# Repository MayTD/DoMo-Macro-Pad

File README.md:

# DoMo Macro Pad

DoMo is a 3x3 macro pad with a rotary encoder and OLED display. It's a straightforward design with a straightforward idea. I originally designed this for myself to provide quick access to most commonly used keys especially for programming. That means the top priority were to include shortcuts for copy and paste! However this can also be used just as any other macro pads for media controls to help improve workflow.

QMK: https://github.com/MayTD/qmk_firmware/tree/master/keyboards/domo

## Features

- QMK Firmware Support
- MX Hot Swap
- OLED Screen
- Rotary Encoder
- LEDS

## Assembly 
Note that source files only covers the PCB. Components must be assembled in order for the board to be functional or completed.
| Number of Parts | Component | Description |
| ------------- | ------------- | ------------- |
| 1 | USB Cable  | Depends on choice of microcontrollers |
| 1 | Pro Micro or Equivalent | Microcontroller that features USB connectivity on-board |
| 1 | Reset Switch | Switch to enter bootloader mode |
| 10 | Diodes | standard switching signal diode | 
| 9 | Kailh MX Sockets | Hot Swapping Sockets which can support MX switches |
| 9 | MX switches | PCB supports PCB Mounted switches | 
| 1 | Rotary Encoder | EC11, 5Pin, 6mm |
| 9 | Keycaps | Any keycaps of choice |
| 1 | Bottom Plate | PCB includes 4 mounting holes that could fit M2 screws | 
| 4 | LEDS | Individual WS2812B 5050 RGB LEDs|
| 4 | 1x4 Connector | 4 pin male header|
| 1 | OLED Display | 0.91 128×32 Display Module|

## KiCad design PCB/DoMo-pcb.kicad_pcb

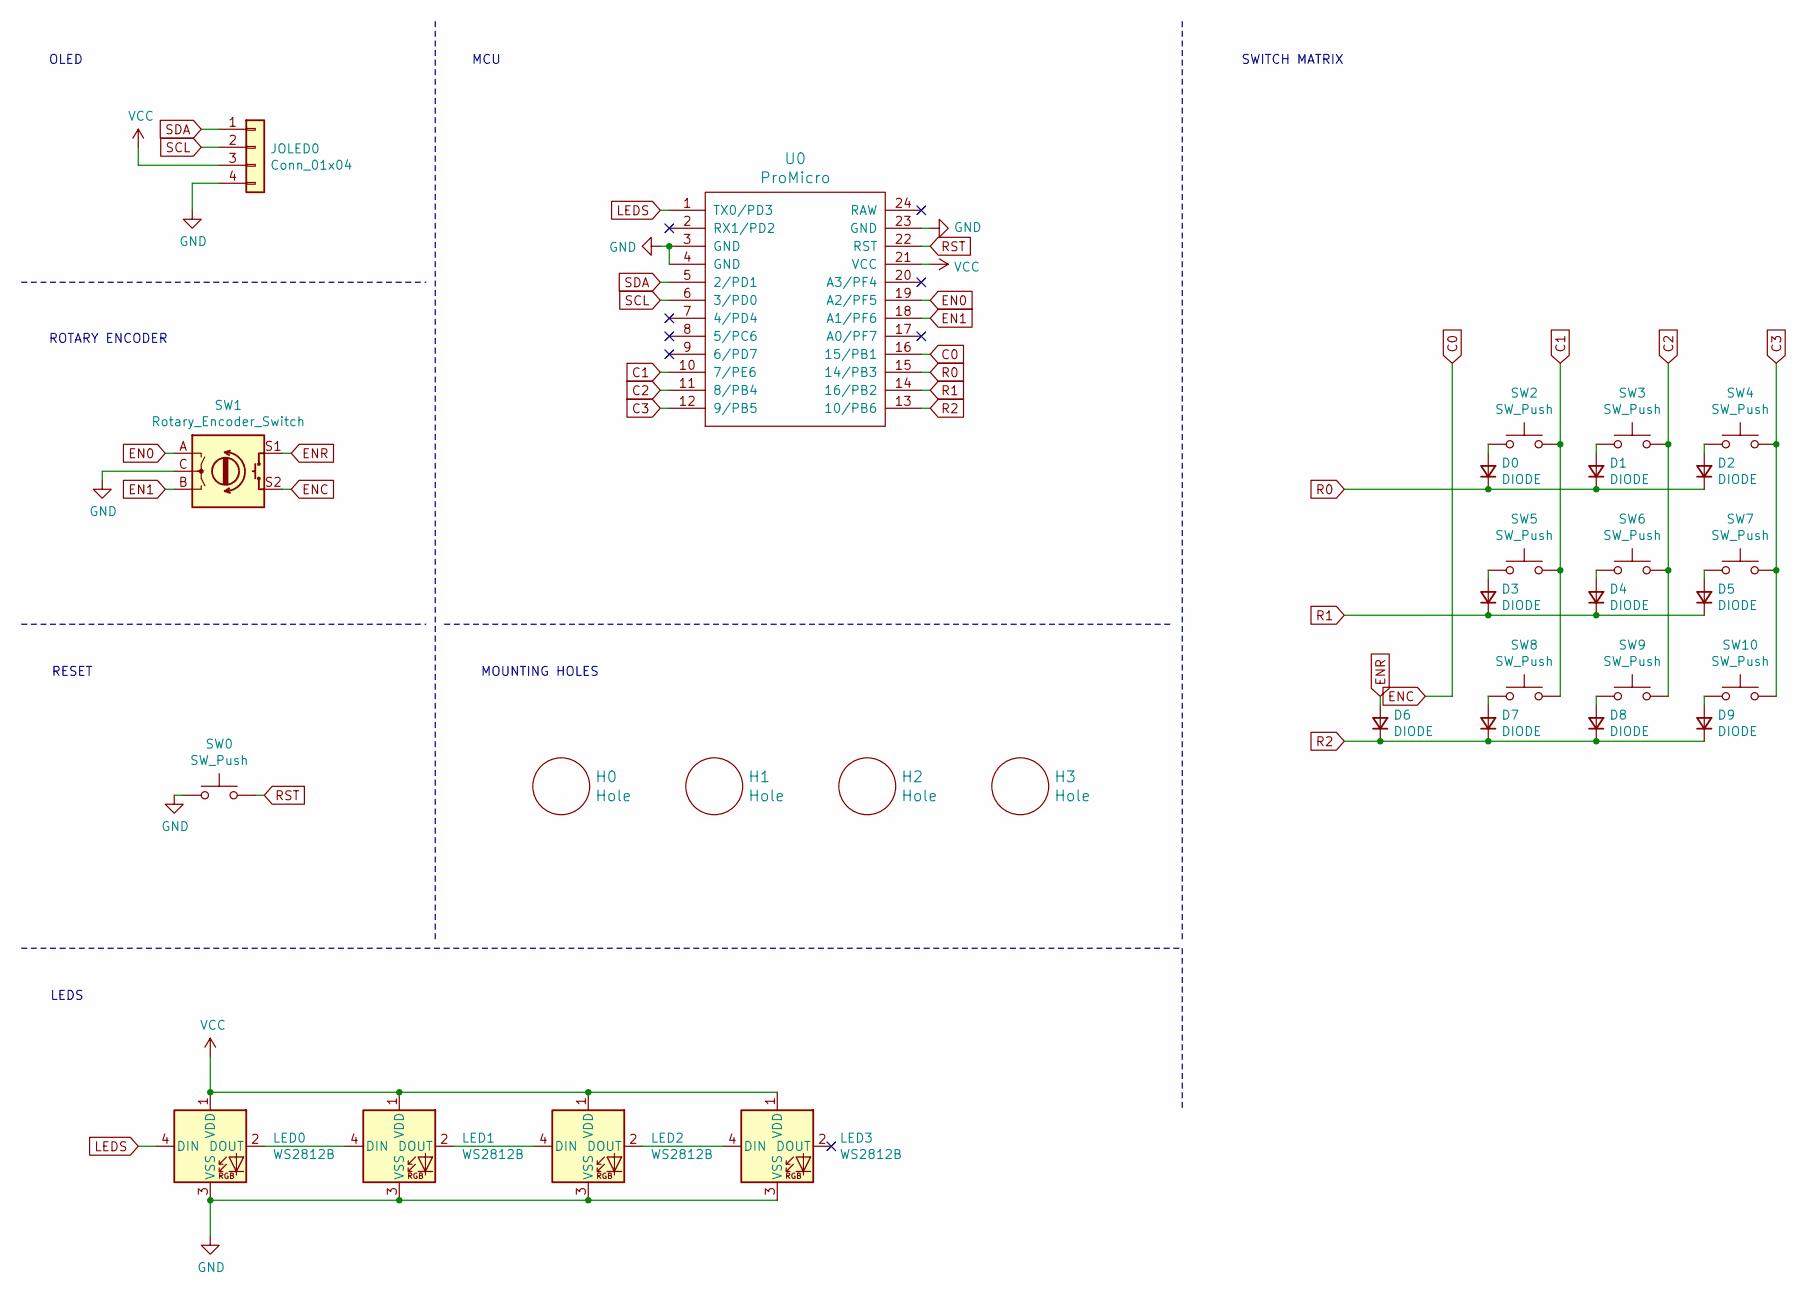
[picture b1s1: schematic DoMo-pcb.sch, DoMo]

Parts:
D0, D1, D2, D3, D4, D5, D6, D7, D8, D9: DIODE; MD_Diode
H0, H1, H2, H3: Hole; MountingHole_2.2mm_M2
JOLED0: Conn_01x04; Pin_Header_Straight_1x04_Pitch2.54mm
LED0, LED1, LED2, LED3: WS2812B; LED_WS2812B-PLCC4
SW0: SW_Push; SW_PUSH_6mm
SW1: Rotary_Encoder_Switch; RotaryEncoder_Alps_EC11E-Switch_Vertical_H20mm
SW2, SW3, SW4, SW5, SW6, SW7, SW8, SW9, SW10: SW_Push; MXOnly-1U-Hotswap
U0: ProMicro; ArduinoProMicro

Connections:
C0: SW1.S2, U0.16 (15/PB1)
C1: SW2.2, SW5.2, SW8.2, U0.10 (7/PE6)
C2: SW3.2, SW6.2, SW9.2, U0.11 (8/PB4)
C3: SW4.2, SW7.2, SW10.2, U0.12 (9/PB5)
EN0: SW1.A, U0.19 (A2/PF5)
EN1: SW1.B, U0.18 (A1/PF6)
ENR: D6.2 (A), SW1.S1
GND: JOLED0.4, LED0.3 (VSS), LED1.3 (VSS), LED2.3 (VSS), LED3.3 (VSS), SW0.1, SW1.C, U0.3 (GND), U0.4 (GND), U0.23 (GND)
LEDS: LED0.4 (DIN), U0.1 (TX0/PD3)
unnamed: D0.2 (A), SW2.1
unnamed: D1.2 (A), SW3.1
unnamed: D2.2 (A), SW4.1
unnamed: D3.2 (A), SW5.1
unnamed: D4.2 (A), SW6.1
unnamed: D5.2 (A), SW7.1
unnamed: D7.2 (A), SW8.1
unnamed: D8.2 (A), SW9.1
unnamed: D9.2 (A), SW10.1
unnamed: LED0.2 (DOUT), LED1.4 (DIN)
unnamed: LED1.2 (DOUT), LED2.4 (DIN)
unnamed: LED2.2 (DOUT), LED3.4 (DIN)
R0: D0.1 (K), D1.1 (K), D2.1 (K), U0.15 (14/PB3)
R1: D3.1 (K), D4.1 (K), D5.1 (K), U0.14 (16/PB2)
R2: D6.1 (K), D7.1 (K), D8.1 (K), D9.1 (K), U0.13 (10/PB6)
RST: SW0.2, U0.22 (RST)
SCL: JOLED0.2, U0.6 (3/PD0)
SDA: JOLED0.1, U0.5 (2/PD1)
VCC: JOLED0.3, LED0.1 (VDD), LED1.1 (VDD), LED2.1 (VDD), LED3.1 (VDD), U0.21 (VCC)

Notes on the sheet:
OLED
LEDS
ROTARY ENCODER
RESET
SWITCH MATRIX
MCU
MOUNTING HOLES

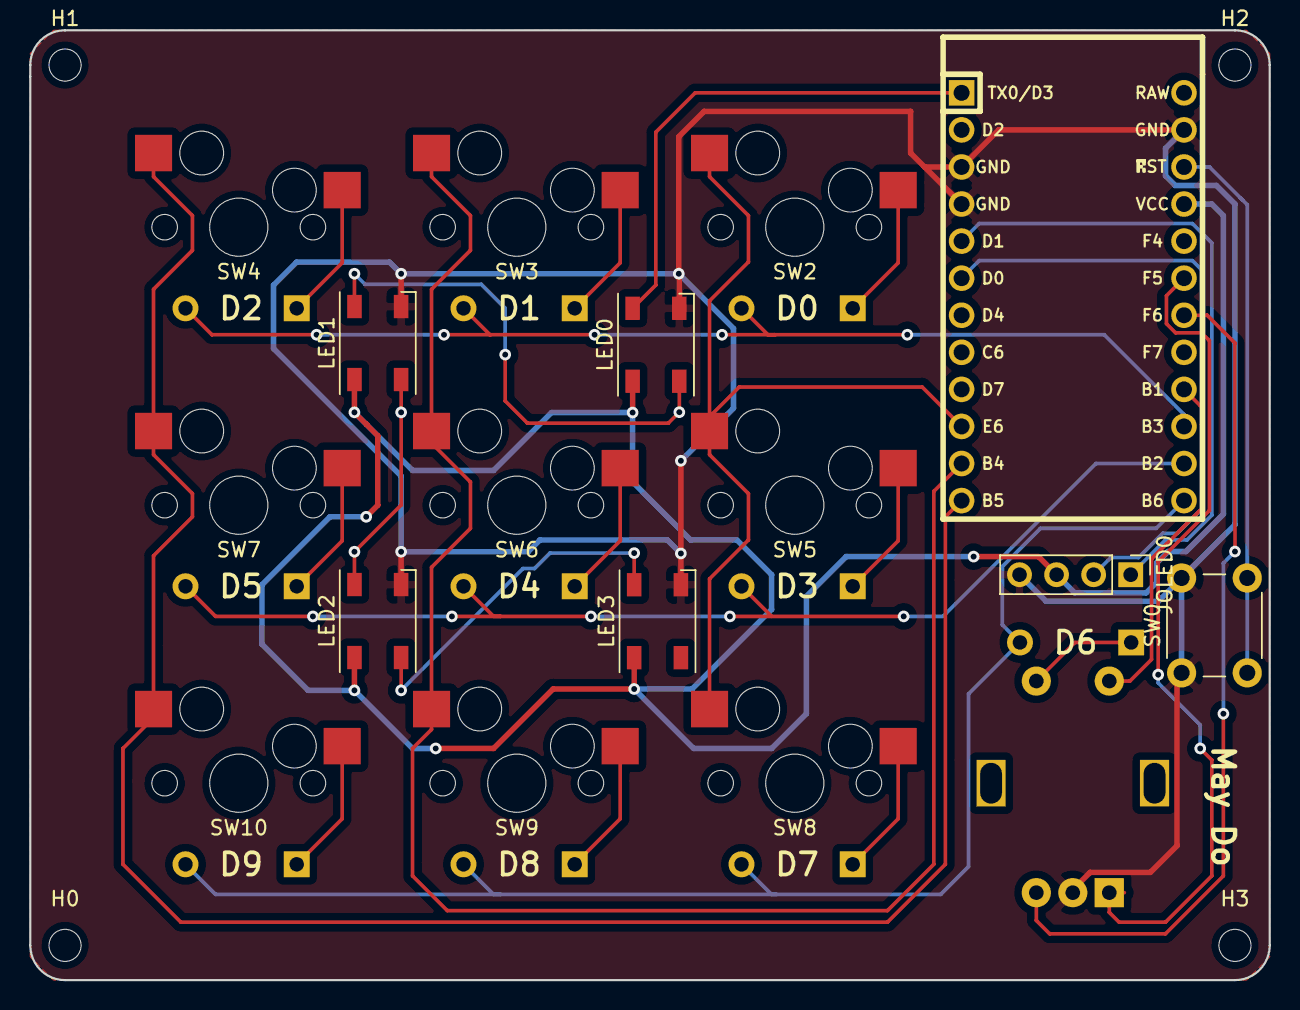
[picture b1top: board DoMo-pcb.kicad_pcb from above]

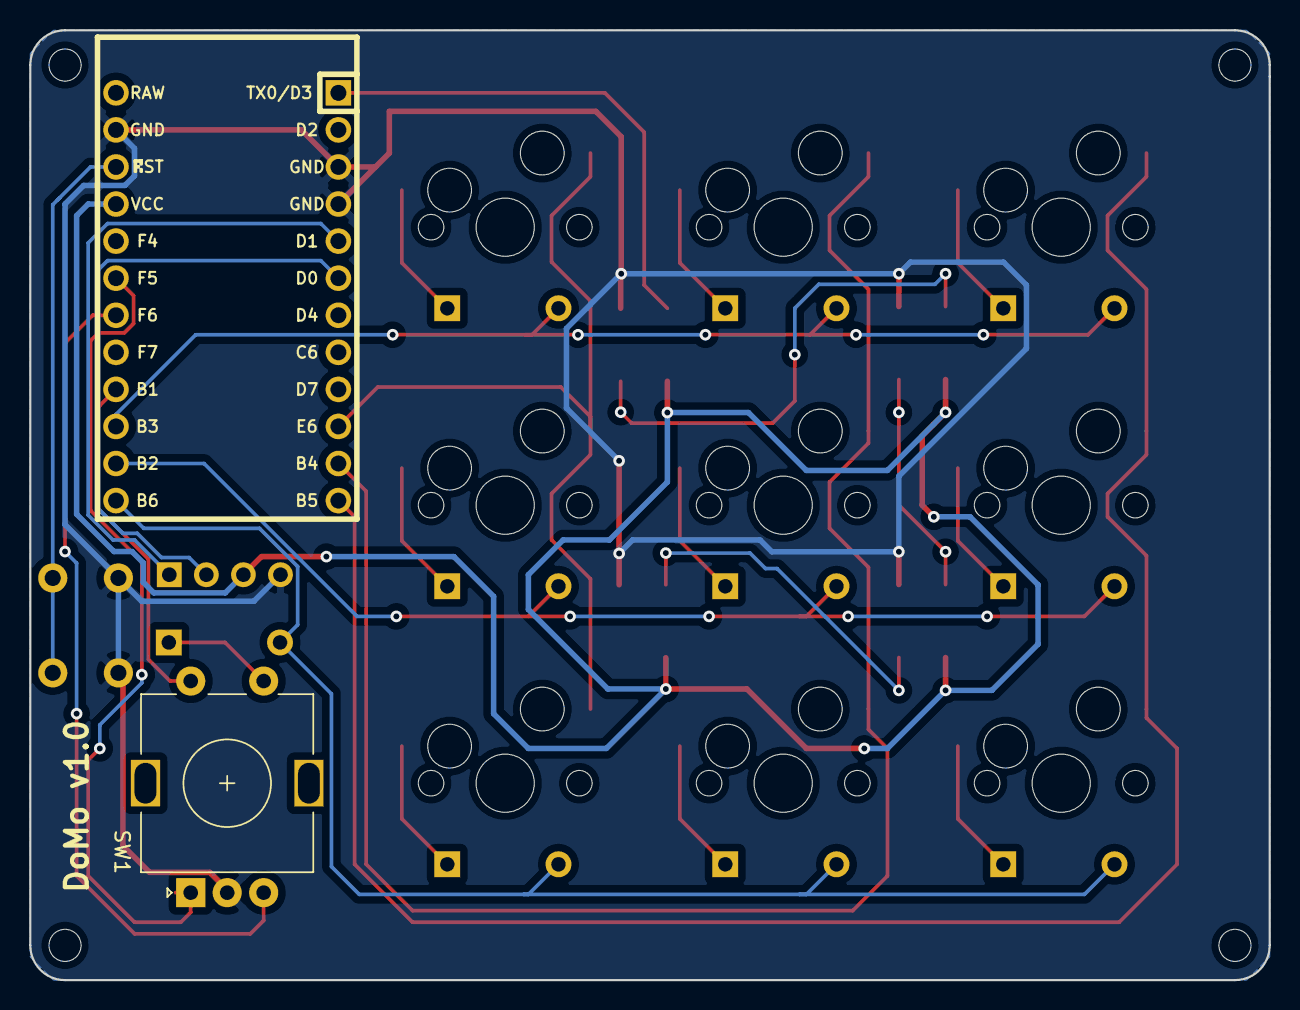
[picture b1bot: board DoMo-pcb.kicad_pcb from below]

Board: 2 copper layers, 84.9 x 65.1 mm, 31 parts (10 on the bottom side), 28 nets.

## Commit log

2020-06-29 add space in readme
2020-06-29 update name
2020-06-29 init pcb
2020-06-29 remove subfolder
2020-06-29 add submodules
2020-06-30 add footprints and symbol libs
2020-07-03 init mcu
2020-07-03 create decoupling capacitors
2020-07-04 create rotary encoder
2020-07-04 create OLED pins
2020-07-04 change submodules
2020-07-04 change mcu to pro micro
2020-07-04 create LEDS
2020-07-05 create matrix
2020-07-05 add mx/alps footprint
2020-07-05 update footprints fields
2020-07-06 pcb layout
2020-07-07 remove 1 led and wire up oled/rotary
2020-07-07 rotary and oled wired up
2020-07-07 wire up col and row
2020-07-07 wire up leds
2020-07-08 remove unconnected routes
2020-07-09 ground fill
2020-07-09 render 3d pcb
2020-07-09 add render to readme
2020-07-09 creat Gerbers
2020-07-10 fix edges
2020-07-10 add front and back render
2020-07-10 add dimensions
2020-07-10 update Gerbers
2020-07-10 Update assembly readme
2020-07-10 Add Diodes to requirements
2020-07-10 fix number of diodes
2020-07-16 Add descriptions of parts
2020-07-25 fix 1x4 connector
2020-07-25 regenerate gerber for connector fix
2020-08-01 add link to QMK fork
